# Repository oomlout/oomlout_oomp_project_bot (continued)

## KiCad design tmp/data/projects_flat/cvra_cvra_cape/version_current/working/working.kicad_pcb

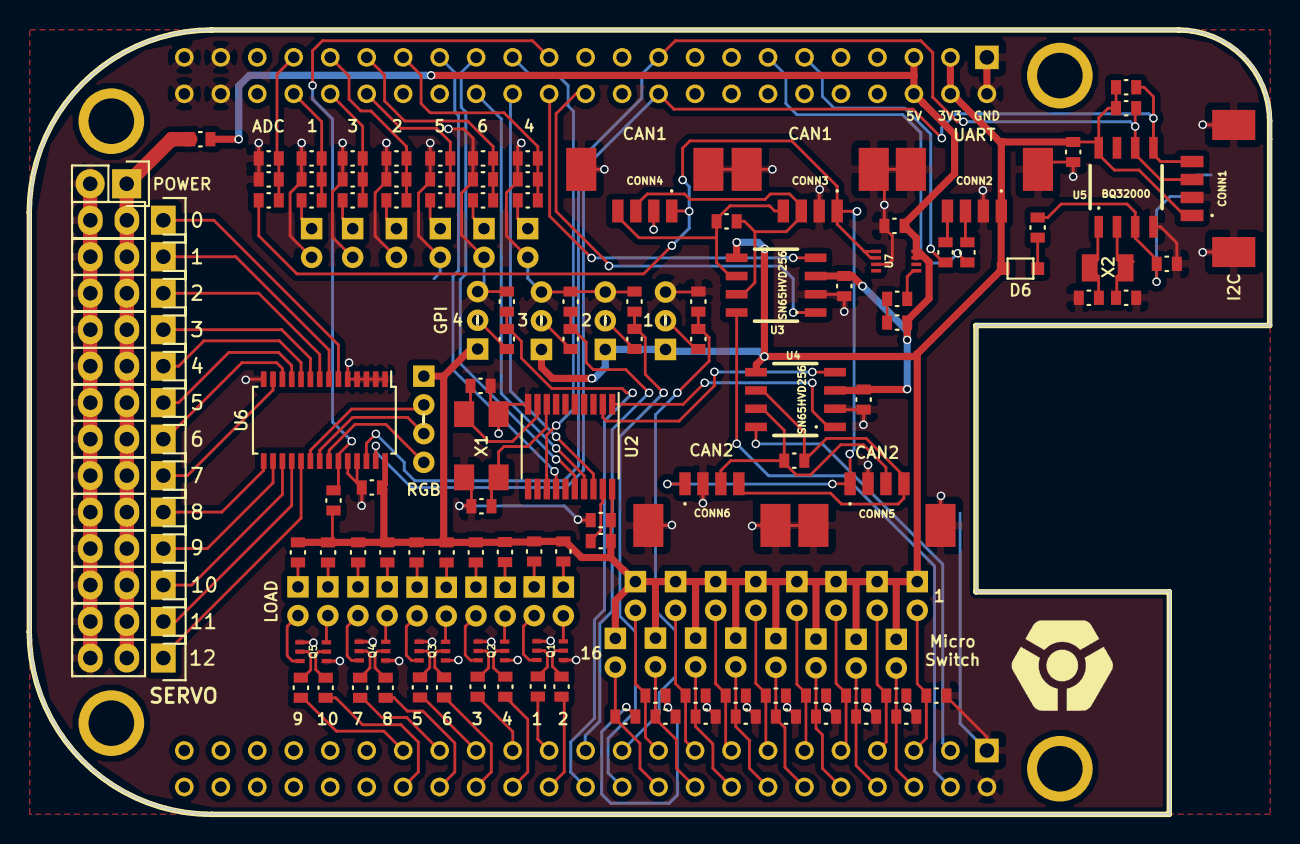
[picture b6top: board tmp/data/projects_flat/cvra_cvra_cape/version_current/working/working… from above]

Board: 2 copper layers, 86.4 x 54.6 mm, 161 parts (1 on the bottom side), 129 nets.

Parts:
0, 1, 2, 3, 4, 5, 6, 7, 8, 9, 10, 11, 12: SERVO; Pin_Header_Straight_1x03
BT1: ML621; Battery_ML621
C1, C3: 30p; _0603
C2, C4, C5, C17: 100n; _0603
C6, C12: 33n; _0603
C7, C8, C9, C10, C11: TBD; _0603
C13: 1u; _0603
C14: 220n; _0603
C15, C16: 10p; _0603
C18: 10u; _0603
CONN1: I2C; _Molex-PicoBlade-SMD-4
CONN2: UART; _Molex-PicoBlade-SMD-4
CONN3, CONN4: CAN1; _Molex-PicoBlade-SMD-4
CONN5, CONN6: CAN2; _Molex-PicoBlade-SMD-4
CONN7, CONN8, CONN9, CONN10, CONN11, CONN12: ADC_2PIN; _Pin2mm_2
CONN13, CONN14, CONN15, CONN16: GPI; _Pin2mm_3
CONN17, CONN18, CONN19, CONN20, CONN25, CONN26, CONN31, CONN32, CONN37, CONN38: LOAD; _Pin2mm_2
CONN40: RGB; _Pin2mm_4
D1: CAN_PWR; _0603
D2, D3, D4, D5: 3.3V; _0603
D6: DB2J314; Diode_SMini2
POWER: Power Connector; Pin_Header_Straight_1x02
Q1, Q2, Q3, Q4, Q5: MBT3904DW1T1; SOT363
R1, R2: 4.7k; _0603
R3: 0; _0603
R4, R5: 330; _0603
R6, R11, R12, R13, R14, R19, R20, R21, R22, R23, R24, R29, R30, R31, R32, R33, R34, R47: 10k; _0603
R7: 8.2k; _0603
R8, R16, R18, R26, R28, R36, R38: 820; _0603
R9, R10: 120; _0603
R15, R17, R25, R27, R35, R45, R46, R50, R51, R54, R55, R58, R59, R62, R63: TBD; _0603
R37: 4.2k; _0603
R39, R40, R41, R42, R43, R44, R48, R49, R52, R53, R56, R57, R60, R61, R64: 1k; _0603
R65: 910; _0603
SW1, SW2, SW3, SW4, SW5, SW6, SW7, SW8, SW9, SW10, SW11, SW12, SW13, SW14, SW15, SW16: MicroSwitch; _Pin2mm_2
U1: BEAGLEBONE
U2: MCP2515_TSSOP; TSSOP20
U3, U4: SN65HVD256; _SO-8
U5: BQ32000; _SO-8
U6: PCA9685; TSSOP28
U7: LTC4362; DFN_8-Lead_2mmx3mm
X1: 8Mhz; XTAL_ABMM2
X2: 32768Hz; XTAL_ABS07

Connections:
+3V3: C2.1, C13.1, C17.1, CONN1.1, CONN2.1, CONN13.1, CONN14.1, CONN15.1, CONN16.1, CONN40.1, D6.2, R1.1, R2.1, R6.2, R45.1, R46.1, R47.1, R50.1, R51.1, R54.1, R55.1, R58.1, R59.1, R62.1, R63.1, SW1.1, SW2.1, SW3.1, SW4.1, SW5.1, SW6.1, SW7.1, SW8.1, SW9.1, SW10.1, SW11.1, SW12.1, SW13.1, SW14.1, SW15.1, SW16.1, U1.C3, U1.C4, U2.20, U3.5, U4.5, U5.8, U6.28
+5V: C4.1, C5.1, C18.2, R3.1, R64.1, U1.C5, U1.C6, U3.3, U4.3, U7.7, U7.8
/ADC_IN_1: C7.1, R15.1, R16.2, U1.C40
/ADC_IN_2: C8.1, R17.1, R18.2, U1.C37
/ADC_IN_3: C9.1, R25.1, R26.2, U1.C38
/ADC_IN_4: C10.1, R27.1, R28.2, U1.C33
/ADC_IN_5: C11.1, R35.1, R36.2, U1.C36
/ADC_IN_6: C12.1, R37.1, R38.2, U1.C35
/Actuators/POWER: 0.2, 1.2, 2.2, 3.2, 4.2, 5.2, 6.2, 7.2, 8.2, 9.2, 10.2, 11.2, 12.2, POWER.1, R3.2
/Actuators/PWM_0: 0.1, U6.6
/Actuators/PWM_1: 1.1, U6.7
/Actuators/PWM_2: 2.1, U6.8
/Actuators/PWM_3: 3.1, U6.9
/Actuators/PWM_4: 4.1, U6.10
/Actuators/PWM_5: 5.1, U6.11
/Actuators/PWM_6: 6.1, U6.12
/Actuators/PWM_7: 7.1, U6.13
/Actuators/PWM_8: 8.1, U6.15
/Actuators/PWM_9: 9.1, U6.16
/Actuators/PWM_10: 10.1, U6.17
/Actuators/PWM_11: 11.1, U6.18
/Actuators/PWM_12: 12.1, U6.19
/Actuators/RGB_LED_B: CONN40.4, U6.22
/Actuators/RGB_LED_G: CONN40.3, U6.21
/Actuators/RGB_LED_R: CONN40.2, U6.20
/CAN1_RX: U1.C24, U3.1
/CAN1_SILENT: U1.B4, U3.8
/CAN1_TX: U1.C26, U3.4
/CAN2_SILENT: U1.B3, U4.8
/D_IN_1: R11.1, SW1.2, U1.B5
/D_IN_2: R12.1, SW2.2, U1.B6
/D_IN_3: R13.1, SW3.2, U1.B7
/D_IN_4: R14.1, SW4.2, U1.B8
/D_IN_5: R19.1, SW5.2, U1.B9
/D_IN_6: R20.1, SW6.2, U1.B10
/D_IN_7: R21.1, SW7.2, U1.B11
/D_IN_8: R22.1, SW8.2, U1.B12
/D_IN_9: R23.1, SW9.2, U1.B13
/D_IN_10: R24.1, SW10.2, U1.B14
/D_IN_11: R29.1, SW11.2, U1.B15
/D_IN_12: R30.1, SW12.2, U1.B16
/D_IN_13: R31.1, SW13.2, U1.B17
/D_IN_14: R32.1, SW14.2, U1.B18
/D_IN_15: R33.1, SW15.2, U1.B19
/D_IN_16: R34.1, SW16.2, U1.B20
/D_IN_17: D2.1, R39.2, U1.B21
/D_IN_18: D3.1, R40.2, U1.B22
/D_IN_19: D4.1, R41.2, U1.B23
/D_IN_20: D5.1, R42.2, U1.B24
/D_OUT_1: R43.2, U1.B25
/D_OUT_2: R44.2, U1.B26
/D_OUT_3: R48.2, U1.B27
/D_OUT_4: R49.2, U1.B28
/D_OUT_5: R52.2, U1.B29
/D_OUT_6: R53.2, U1.B30
/D_OUT_7: R56.2, U1.B31
/D_OUT_8: R57.2, U1.B32
/D_OUT_9: R60.2, U1.B33
/D_OUT_10: R61.2, U1.B34
/I2C2_SCL: CONN1.3, R2.2, U1.C19, U5.6, U6.26
/I2C2_SDA: CONN1.4, R1.2, U1.C20, U5.5, U6.27
/PWMGEN_OE: R47.2, U1.C25, U6.23
/SPI_CAN_CS: U1.C28, U2.18
/SPI_CAN_INT: U1.C27, U2.13
/SPI_CAN_MISO: U1.C30, U2.17
/SPI_CAN_MOSI: U1.C29, U2.16
/SPI_CAN_SCK: U1.C31, U2.14
/UART4_RX: R5.2, U1.C11
/UART4_TX: R4.2, U1.C13
/V_CAN_BUS: CONN3.1, CONN4.1, CONN5.1, CONN6.1, R7.1, U7.1, U7.2
/V_CAN_BUS_SENSE: C6.1, R7.2, R8.1, U1.C39
GND: 0.3, 1.3, 2.3, 3.3, 4.3, 5.3, 6.3, 7.3, 8.3, 9.3, 10.3, 11.3, 12.3, BT1.2, C1.2, C2.2, C3.2, C4.2, C5.2, C6.2, C7.2, C8.2, C9.2, C10.2, C11.2, C12.2, C13.2, C14.2, C15.2, C16.2, C17.2, C18.1, CONN1.2, CONN1.MECH, CONN2.2, CONN2.MECH, CONN3.2, CONN3.MECH, CONN4.2, CONN4.MECH, CONN5.2, CONN5.MECH, CONN6.2, CONN6.MECH, CONN7.2, CONN8.2, CONN9.2, CONN10.2, CONN11.2, CONN12.2, CONN13.3, CONN14.3, CONN15.3, CONN16.3, D2.2, D3.2, D4.2, D5.2, POWER.2, Q1.1, Q1.4, Q2.1, Q2.4, Q3.1, Q3.4, Q4.1, Q4.4, Q5.1, Q5.4, R8.2, R11.2, R12.2, R13.2, R14.2, R16.1, R18.1, R19.2, R20.2, R21.2, R22.2, R23.2, R24.2, R26.1, R28.1, R29.2, R30.2, R31.2, R32.2, R33.2, R34.2, R36.1, R38.1, U1.B1, U1.B2, U1.C1, U1.C2, U1.C34, U1.C43, U1.C44, U1.C45, U1.C46, U2.10, U3.2, U4.2, U5.4, U6.1, U6.2, U6.3, U6.4, U6.5, U6.14, U6.24, U6.25, U7.3, X1.2, X1.4
unnamed: BT1.1, C14.1, R65.2, U5.3
unnamed: C1.1, U2.8, X1.1
unnamed: C3.1, U2.9, X1.3
unnamed: C15.1, U5.2, X2.1
unnamed: C16.1, U5.1, X2.2
unnamed: CONN2.3, R4.1
unnamed: CONN2.4, R5.1
unnamed: CONN3.3, CONN4.3, R9.1, U3.7
unnamed: CONN3.4, CONN4.4, R9.2, U3.6
unnamed: CONN5.3, CONN6.3, R10.1, U4.7
unnamed: CONN5.4, CONN6.4, R10.2, U4.6
unnamed: CONN7.1, R15.2
unnamed: CONN8.1, R17.2
unnamed: CONN9.1, R25.2
unnamed: CONN10.1, R27.2
unnamed: CONN11.1, R35.2
unnamed: CONN12.1, R37.2
unnamed: CONN13.2, R39.1
unnamed: CONN14.2, R40.1
unnamed: CONN15.2, R41.1
unnamed: CONN16.2, R42.1
unnamed: CONN17.1, R45.2
unnamed: CONN17.2, Q1.3
unnamed: CONN18.1, R46.2
unnamed: CONN18.2, Q1.6
unnamed: CONN19.1, R50.2
unnamed: CONN19.2, Q2.3
unnamed: CONN20.1, R51.2
unnamed: CONN20.2, Q2.6
unnamed: CONN25.1, R54.2
unnamed: CONN25.2, Q3.3
unnamed: CONN26.1, R55.2
unnamed: CONN26.2, Q3.6
unnamed: CONN31.1, R58.2
unnamed: CONN31.2, Q4.3
unnamed: CONN32.1, R59.2
unnamed: CONN32.2, Q4.6
unnamed: CONN37.1, R62.2
unnamed: CONN37.2, Q5.3
unnamed: CONN38.1, R63.2
unnamed: CONN38.2, Q5.6
unnamed: D1.1, U7.5
unnamed: D1.2, R64.2
unnamed: D6.1, R65.1
unnamed: Q1.2, R44.1
unnamed: Q1.5, R43.1
unnamed: Q2.2, R49.1
unnamed: Q2.5, R48.1
unnamed: Q3.2, R53.1
unnamed: Q3.5, R52.1
unnamed: Q4.2, R57.1
unnamed: Q4.5, R56.1
unnamed: Q5.2, R61.1
unnamed: Q5.5, R60.1
unnamed: R6.1, U2.19
unnamed: U2.1, U4.1
unnamed: U2.2, U4.4

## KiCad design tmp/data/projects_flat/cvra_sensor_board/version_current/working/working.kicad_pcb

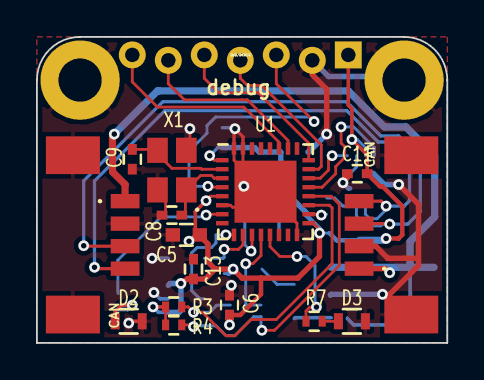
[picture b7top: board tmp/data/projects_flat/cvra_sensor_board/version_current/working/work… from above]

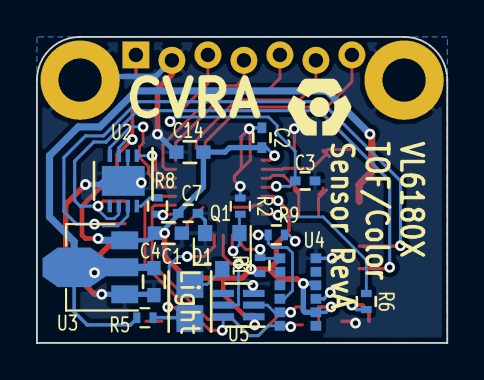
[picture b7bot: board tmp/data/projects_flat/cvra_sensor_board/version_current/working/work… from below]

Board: 2 copper layers, 22.8 x 17.0 mm, 36 parts (18 on the bottom side), 28 nets.

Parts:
C1, C14: 4.7uF; C_0603
C2, C3, C6, C7, C11, C13: 0.1uF; C_0402
C4: 1uF; C_0603
C5: 10uF; C_0603
C8, C9: 10pF; C_0402
CONN1: SWD/DEBUG; _Pin2mm_7z
CONN2, CONN3: CAN; _Molex-PicoBlade-SMD-4
D1: Light; LED_CREE_CLM3A
D2: LTST-S270KGKT; R_0603
D3: LTST-S270KRKT; R_0603
MEC1, MEC2: MEC; _M2
Q1: BSS138; SOT-23
R1, R2, R9: 47k; R_0402
R3, R4: 4.7k; R_0402
R5, R6, R7, R8: 1k; R_0402
U1: STM32F302K8U6; QFN-32-1EP_5x5mm_Pitch0.5mm
U2: LTC2875IDD#PBF; DFN-8-1EP_3x3mm_Pitch0.5mm
U3: MCP1703-MB; SOT-89-3
U4: VL6180X
U5: TCS3472X; DFN-6-_2x2.4x0.65mm_P0.65mm
X1: 16MHz; _TSX-3225-SMD-XTAL

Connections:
+5V: C4.1, CONN2.1, CONN3.1, R5.2, U3.2
/CAN_RX: U1.21, U2.4
/CAN_SPEED: R8.2, U1.18
/CAN_TX: U1.22, U2.1
/Error: R7.1, U1.13
/GPIO0: R9.2, U1.9, U4.4
/GPIO1: R1.2, U1.10, U4.1
/I2C_SCL: R3.2, U1.19, U4.5, U5.2
/I2C_SDA: R4.2, U1.20, U4.6, U5.6
/LIGHT_EN: Q1.1, R2.2, U1.11
/LIGHT_INT: U1.12, U5.5
/Proximity: R6.1, U1.7
/STM32_NRST: C3.1, CONN1.3, U1.4
/STM32_SWCLK: CONN1.5, U1.24
/STM32_SWDIO: CONN1.4, U1.23
/UART2_RX: CONN1.7, U1.27
/UART2_TX: CONN1.6, U1.26
GND: C1.2, C2.2, C3.2, C4.2, C5.2, C6.2, C7.2, C8.2, C9.2, C11.2, C13.2, C14.2, CONN1.2, CONN2.2, CONN2.MECH, CONN3.2, CONN3.MECH, D2.1, D3.1, MEC1.1, MEC2.1, Q1.2, R2.1, U1.6, U1.16, U1.31, U1.32, U1.33, U2.2, U2.9, U3.1, U4.9, U4.12, U5.3, X1.2, X1.4
unnamed: C8.1, U1.3, X1.1
unnamed: C9.1, U1.2, X1.3
unnamed: CONN2.3, CONN3.3, U2.7
unnamed: CONN2.4, CONN3.4, U2.6
unnamed: D1.1, Q1.3
unnamed: D1.2, R5.1
unnamed: D2.2, R6.2
unnamed: D3.2, R7.2
unnamed: R8.1, U2.8
VCC: C1.1, C2.1, C5.1, C6.1, C7.1, C11.1, C13.1, C14.1, CONN1.1, R1.1, R3.1, R4.1, R9.1, U1.1, U1.5, U1.17, U2.3, U3.3, U4.8, U4.10, U5.1

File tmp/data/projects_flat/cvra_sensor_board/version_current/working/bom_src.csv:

Id,Ref,Boitier,Qu,Qu Boards,Designation,No Digikey,Nb. boards,5
1,D1,LED_CREE_CLM3A,1,5,CLM3C-MKW-CW,CLM3C-MKW-CWAXB233CT-ND,,
2,"C1,C14",C_0603,2,10,4.7uF,445-7482-1-ND,,
3,"R6,R7,R8,R5",R_0402,4,20,1k,311-1.00KLRCT-ND,,
4,C4,C_0603,1,5,1uF,1276-1182-1-ND,,
5,"C11,C2,C3,C7,C13,C6",C_0402,6,30,0.1uF,490-13341-1-ND,,
7,C5,C_0603,1,5,10uF,490-10474-1-ND,,
8,"C8,C9",C_0402,2,10,10pF,490-6186-1-ND,,
9,"CONN2,CONN3",_Molex-PicoBlade-SMD-4,2,10,WM7622CT-ND,WM7622CT-ND,,
10,"R1,R9,R2",R_0402,3,15,47k,311-47.0KLRCT-ND,,
11,"R3,R4",R_0402,2,10,4.7k,ERJ-2RKF4701X,,
12,U1,QFN-32-1EP_5x5mm_Pitch0.5mm,1,5,STM32F302K8U6,STM32F302K8U6,,
13,U2,DFN-8-1EP_3x3mm_Pitch0.5mm,1,5,LTC2875IDD#PBF,LTC2875IDD#PBF,,
14,X1,_TSX-3225-SMD-XTAL,1,5,16MHz,FL1600087CT-ND,,
16,D2,R_0603,1,5,LTST-S270KGKT,160-1478-1-ND,,
17,D3,R_0603,1,5,LTST-S270KRKT,160-1479-1-ND,,
18,Q1,SOT-23,1,5,BSS138,BSS138LT1GOSCT-ND,,
19,U5,DFN-6-_2x2.4x0.65mm_P0.65mm,1,5,TCS3472X,TCS34725FNCT-ND,,
20,U4,VL6180X,1,5,VL6180X,497-14702-1-ND,,
21,CONN1,_Pin2mm_7z,1,5,,,,
22,U3,SOT-89-3,1,5,MCP1703-MB,MCP1703T-3002E/MBCT-ND,,

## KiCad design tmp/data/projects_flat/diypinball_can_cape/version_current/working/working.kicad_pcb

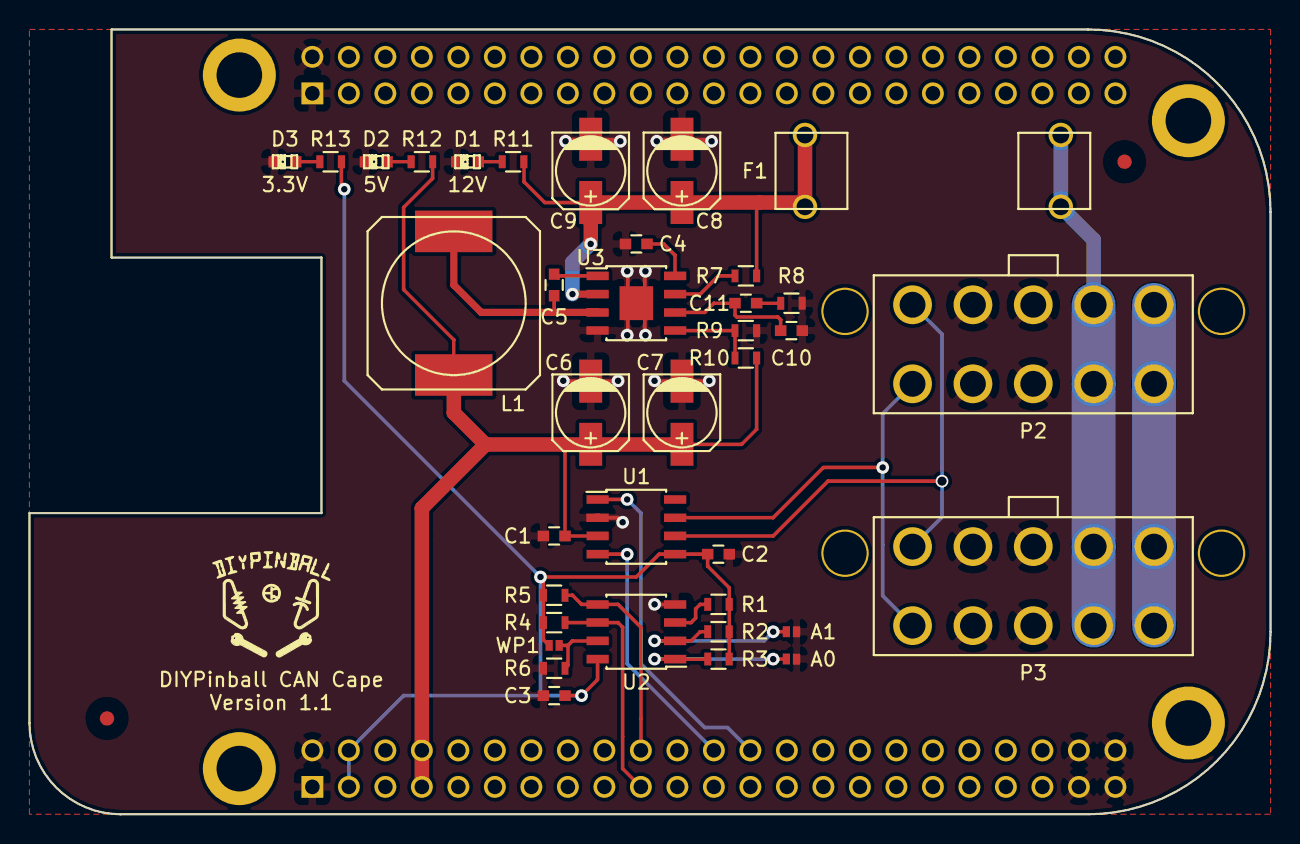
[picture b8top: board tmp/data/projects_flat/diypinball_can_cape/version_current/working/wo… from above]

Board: 2 copper layers, 86.4 x 54.6 mm, 40 parts (0 on the bottom side), 26 nets.

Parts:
A0, A1: JUMPER; S_JUMPER_2
C1, C2, C3, C4: 100n; C_0603
C5: 10n; C_0603
C6, C7: 22u; c_elec_5x5.8
C8, C9: 10u; c_elec_5x5.8
C10: NP; C_0603
C11: 3.3n; C_0603
D1, D2, D3: LED; LED-0603
F1: FUSE; FC203-20MM
FIDUCIAL: VAL**; FIDUCIAL
FIDUCIAL#2: VAL**; FIDUCIAL
L1: 4.7u; SELF-WE-PD-XXL
P1: BEAGLEBONE_BLACK
P2, P3: PINBALL-CONNECTOR; PINBALL-CONNECTOR-V
R1, R2, R3, R4, R5, R6, R11: 4.7K; R_0603
R7: 10K; R_0603
R8: 13K; R_0603
R9: 11.8K; R_0603
R10: 53.6K; R_0603
R12, R13: 1K; R_0603
U1: MCP2562; SOIC-8_3.9x4.9mm_Pitch1.27mm
U2: 24C256; SOIC-8_3.9x4.9mm_Pitch1.27mm
U3: AP3513E; SOIC-8-1EP_3.9x4.9mm_Pitch1.27mm
WP1: JUMPER; S_JUMPER_2

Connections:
+3.3V: C2.1, C3.1, P1.B3, P1.B4, R1.1, R2.1, R3.1, R4.1, R5.1, R13.1, U1.5, U2.8, WP1.1
+5V: C1.1, C6.1, C7.1, L1.2, P1.B7, P1.B8, R10.2, R12.1, U1.3
+12V: C8.1, C9.1, F1.2, R7.2, R11.1, U3.2
CANH: P2.5, P3.5, U1.7
CANL: P2.10, P3.10, U1.6
CANRX: P1.B24, U1.4
CANTX: P1.B26, U1.1
GND: A0.1, A1.1, C1.2, C2.2, C3.2, C4.2, C6.2, C7.2, C8.2, C9.2, C10.2, D1.1, D2.1, D3.1, P1.A1, P1.A2, P1.B1, P1.B2, P1.B43, P1.B44, P1.B45, P1.B46, P2.3, P2.4, P2.8, P2.9, P3.3, P3.4, P3.8, P3.9, R6.2, R8.1, R9.1, U1.2, U2.4, U3.4, U3.9
unnamed: A0.2, R3.2, U2.1
unnamed: A1.2, R2.2, U2.2
unnamed: C4.1, U3.8
unnamed: C5.1, L1.1, U3.3
unnamed: C5.2, U3.1
unnamed: C10.1, C11.1, U3.6
unnamed: C11.2, R8.2
unnamed: D1.2, R11.2
unnamed: D2.2, R12.2
unnamed: D3.2, R13.2
unnamed: F1.1, P2.2, P2.7, P3.2, P3.7
unnamed: P2.1, P2.6, P3.1, P3.6
unnamed: R1.2, U2.3
unnamed: R6.1, U2.7, WP1.2
unnamed: R7.1, U3.7
unnamed: R9.2, R10.1, U3.5
SCL: P1.B19, R4.2, U2.6
SDA: P1.B20, R5.2, U2.5
